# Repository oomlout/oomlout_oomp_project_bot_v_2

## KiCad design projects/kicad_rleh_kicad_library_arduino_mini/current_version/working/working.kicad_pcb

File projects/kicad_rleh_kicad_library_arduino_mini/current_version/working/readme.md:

# kicad_library
 
## summary 
* id: kicad_rleh_kicad_library_arduino_mini
* user: kicad_rleh
* name: kicad_library
* board: arduino_mini
* repo: https://github.com/kicad-rleh/kicad-library
* src_file_repo_kicad_pcb: template/Arduino_Mini/Arduino_Mini.kicad_pcb
* src_file_repo_kicad_pcb_link: https://github.com/kicad-rleh/kicad-library/tree/master/template/Arduino_Mini/Arduino_Mini.kicad_pcb

* src_file_repo_sch: template/Arduino_Mini/Arduino_Mini.sch
* src_file_repo_sch_link: https://github.com/kicad-rleh/kicad-library/tree/master/template/Arduino_Mini/Arduino_Mini.sch
* full details link: https://github.com/oomlout/oomlout_oomp_project_bot_v_2/tree/main/projects/kicad_rleh_kicad_library_arduino_mini/current_version/working

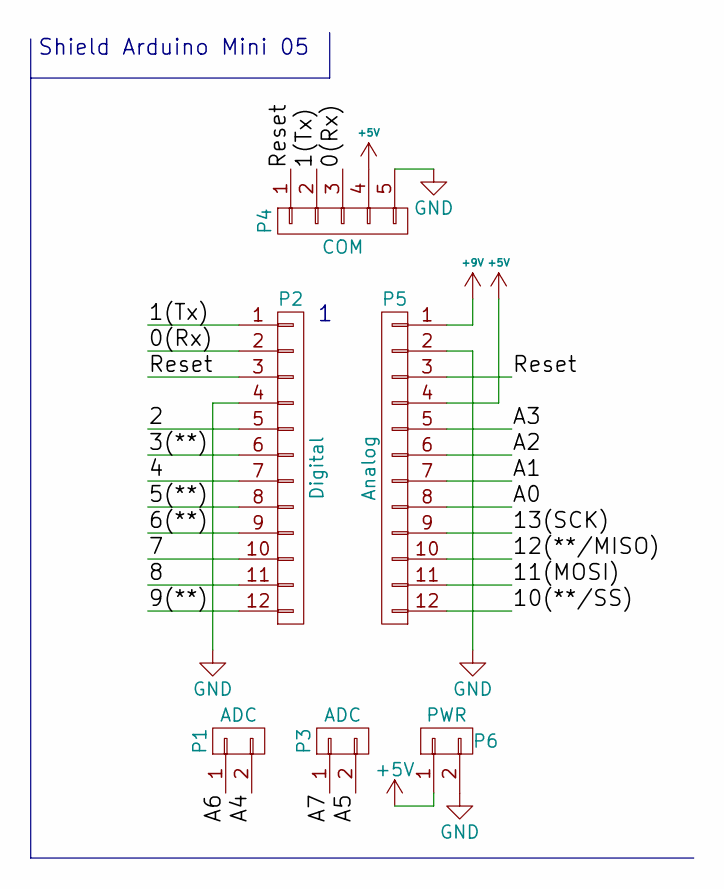
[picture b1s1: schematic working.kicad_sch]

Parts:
P1, P3: ADC; Socket_Strip_Arduino_1x02
P2: Digital; Socket_Strip_Arduino_1x12
P4: COM; Socket_Strip_Arduino_1x05
P5: Analog; Socket_Strip_Arduino_1x12
P6: PWR; Socket_Strip_Arduino_1x02

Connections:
+5V: P4.4, P5.4, P6.1
+9V: P5.1
/0(Rx): P2.2, P4.3
/1(Tx): P2.1, P4.2
/2: P2.5
/3(**): P2.6
/4: P2.7
/5(**): P2.8
/6(**): P2.9
/7: P2.10
/8: P2.11
/9(**): P2.12
/10(**/SS): P5.12
/11(MOSI): P5.11
/12(**/MISO): P5.10
/13(SCK): P5.9
/A0: P5.8
/A1: P5.7
/A2: P5.6
/A3: P5.5
/A4: P1.2
/A5: P3.2
/A6: P1.1
/A7: P3.1
/Reset: P2.3, P4.1, P5.3
GND: P2.4, P4.5, P5.2, P6.2

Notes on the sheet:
Shield Arduino Mini 05

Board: 2 copper layers, 6 parts (0 on the bottom side), 5 nets, no tracks yet.

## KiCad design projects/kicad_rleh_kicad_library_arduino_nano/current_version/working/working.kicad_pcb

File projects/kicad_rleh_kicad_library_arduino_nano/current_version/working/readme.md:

# kicad_library
 
## summary 
* id: kicad_rleh_kicad_library_arduino_nano
* user: kicad_rleh
* name: kicad_library
* board: arduino_nano
* repo: https://github.com/kicad-rleh/kicad-library
* src_file_repo_kicad_pcb: template/Arduino_Nano/Arduino_Nano.kicad_pcb
* src_file_repo_kicad_pcb_link: https://github.com/kicad-rleh/kicad-library/tree/master/template/Arduino_Nano/Arduino_Nano.kicad_pcb

* src_file_repo_sch: template/Arduino_Nano/Arduino_Nano.sch
* src_file_repo_sch_link: https://github.com/kicad-rleh/kicad-library/tree/master/template/Arduino_Nano/Arduino_Nano.sch
* full details link: https://github.com/oomlout/oomlout_oomp_project_bot_v_2/tree/main/projects/kicad_rleh_kicad_library_arduino_nano/current_version/working

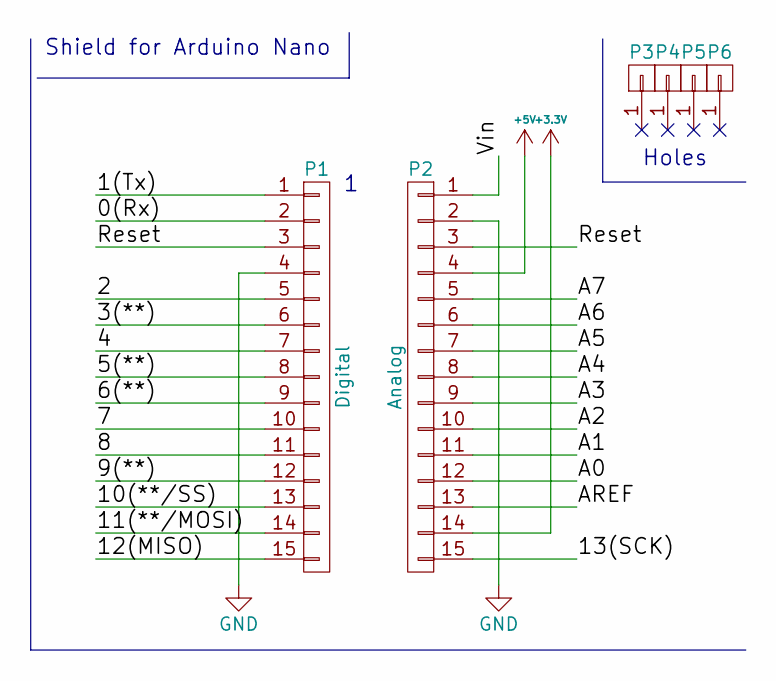
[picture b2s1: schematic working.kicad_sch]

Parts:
P1: Digital; Socket_Strip_Arduino_1x15
P2: Analog; Socket_Strip_Arduino_1x15
P3, P4, P5, P6: CONN_01X01; 1pin_Nano

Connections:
+3V3: P2.14
+5V: P2.4
/0(Rx): P1.2
/1(Tx): P1.1
/2: P1.5
/3(**): P1.6
/4: P1.7
/5(**): P1.8
/6(**): P1.9
/7: P1.10
/8: P1.11
/9(**): P1.12
/10(**/SS): P1.13
/11(**/MOSI): P1.14
/12(MISO): P1.15
/13(SCK): P2.15
/A0: P2.12
/A1: P2.11
/A2: P2.10
/A3: P2.9
/A4: P2.8
/A5: P2.7
/A6: P2.6
/A7: P2.5
/AREF: P2.13
/Reset: P1.3, P2.3
/Vin: P2.1
GND: P1.4, P2.2

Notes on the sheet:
Holes
Shield for Arduino Nano

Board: 2 copper layers, 6 parts (0 on the bottom side), 2 nets, no tracks yet.

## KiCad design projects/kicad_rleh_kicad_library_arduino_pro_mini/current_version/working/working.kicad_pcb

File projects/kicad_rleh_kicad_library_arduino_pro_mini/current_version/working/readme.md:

# kicad_library
 
## summary 
* id: kicad_rleh_kicad_library_arduino_pro_mini
* user: kicad_rleh
* name: kicad_library
* board: arduino_pro_mini
* repo: https://github.com/kicad-rleh/kicad-library
* src_file_repo_kicad_pcb: template/Arduino_Pro_Mini/Arduino_Pro_Mini.kicad_pcb
* src_file_repo_kicad_pcb_link: https://github.com/kicad-rleh/kicad-library/tree/master/template/Arduino_Pro_Mini/Arduino_Pro_Mini.kicad_pcb

* src_file_repo_sch: template/Arduino_Pro_Mini/Arduino_Pro_Mini.sch
* src_file_repo_sch_link: https://github.com/kicad-rleh/kicad-library/tree/master/template/Arduino_Pro_Mini/Arduino_Pro_Mini.sch
* full details link: https://github.com/oomlout/oomlout_oomp_project_bot_v_2/tree/main/projects/kicad_rleh_kicad_library_arduino_pro_mini/current_version/working

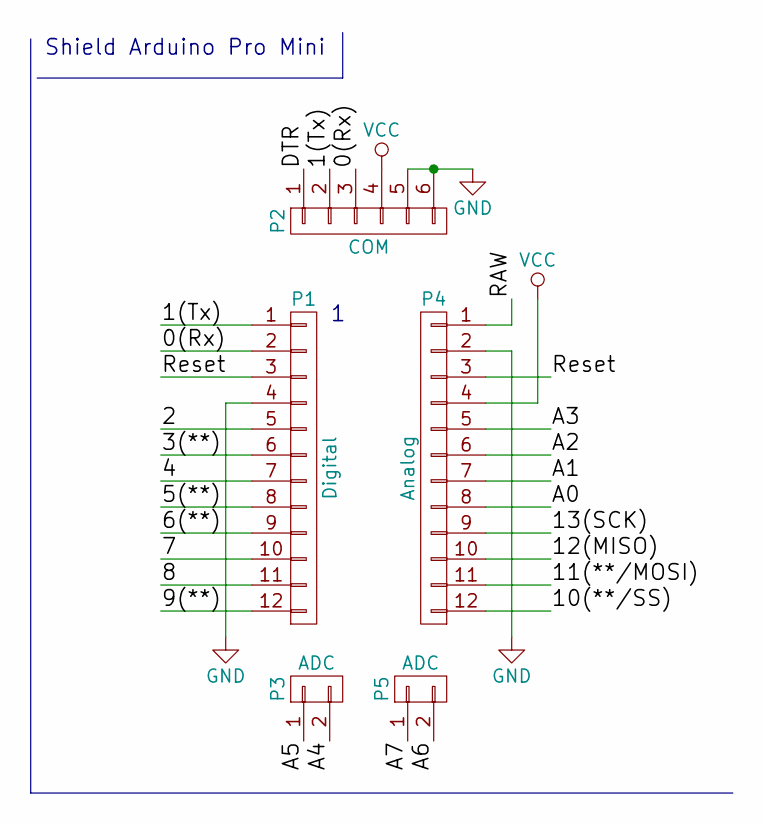
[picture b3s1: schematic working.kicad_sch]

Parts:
P1: Digital; Socket_Strip_Arduino_1x12
P2: COM; Socket_Strip_Arduino_1x06
P3, P5: ADC; Socket_Strip_Arduino_1x02
P4: Analog; Socket_Strip_Arduino_1x12

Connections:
/0(Rx): P1.2, P2.3
/1(Tx): P1.1, P2.2
/2: P1.5
/3(**): P1.6
/4: P1.7
/5(**): P1.8
/6(**): P1.9
/7: P1.10
/8: P1.11
/9(**): P1.12
/10(**/SS): P4.12
/11(**/MOSI): P4.11
/12(MISO): P4.10
/13(SCK): P4.9
/A0: P4.8
/A1: P4.7
/A2: P4.6
/A3: P4.5
/A4: P3.2
/A5: P3.1
/A6: P5.2
/A7: P5.1
/DTR: P2.1
/RAW: P4.1
/Reset: P1.3, P4.3
GND: P1.4, P2.5, P2.6, P4.2
VCC: P2.4, P4.4

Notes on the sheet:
Shield Arduino Pro Mini

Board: 2 copper layers, 5 parts (0 on the bottom side), 5 nets, no tracks yet.

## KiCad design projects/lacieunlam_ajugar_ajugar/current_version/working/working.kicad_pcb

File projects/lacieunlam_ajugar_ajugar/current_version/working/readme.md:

# ajugar
 
## summary 
* id: lacieunlam_ajugar_ajugar
* user: lacieunlam
* name: ajugar
* board: ajugar
* repo: https://github.com/LacieUnlam/Ajugar
* src_file_repo_kicad_pcb: AjugarV2/Ajugar.kicad_pcb
* src_file_repo_kicad_pcb_link: https://github.com/LacieUnlam/Ajugar/tree/master/AjugarV2/Ajugar.kicad_pcb

* src_file_repo_sch: AjugarV2/Ajugar.sch
* src_file_repo_sch_link: https://github.com/LacieUnlam/Ajugar/tree/master/AjugarV2/Ajugar.sch
* full details link: https://github.com/oomlout/oomlout_oomp_project_bot_v_2/tree/main/projects/lacieunlam_ajugar_ajugar/current_version/working

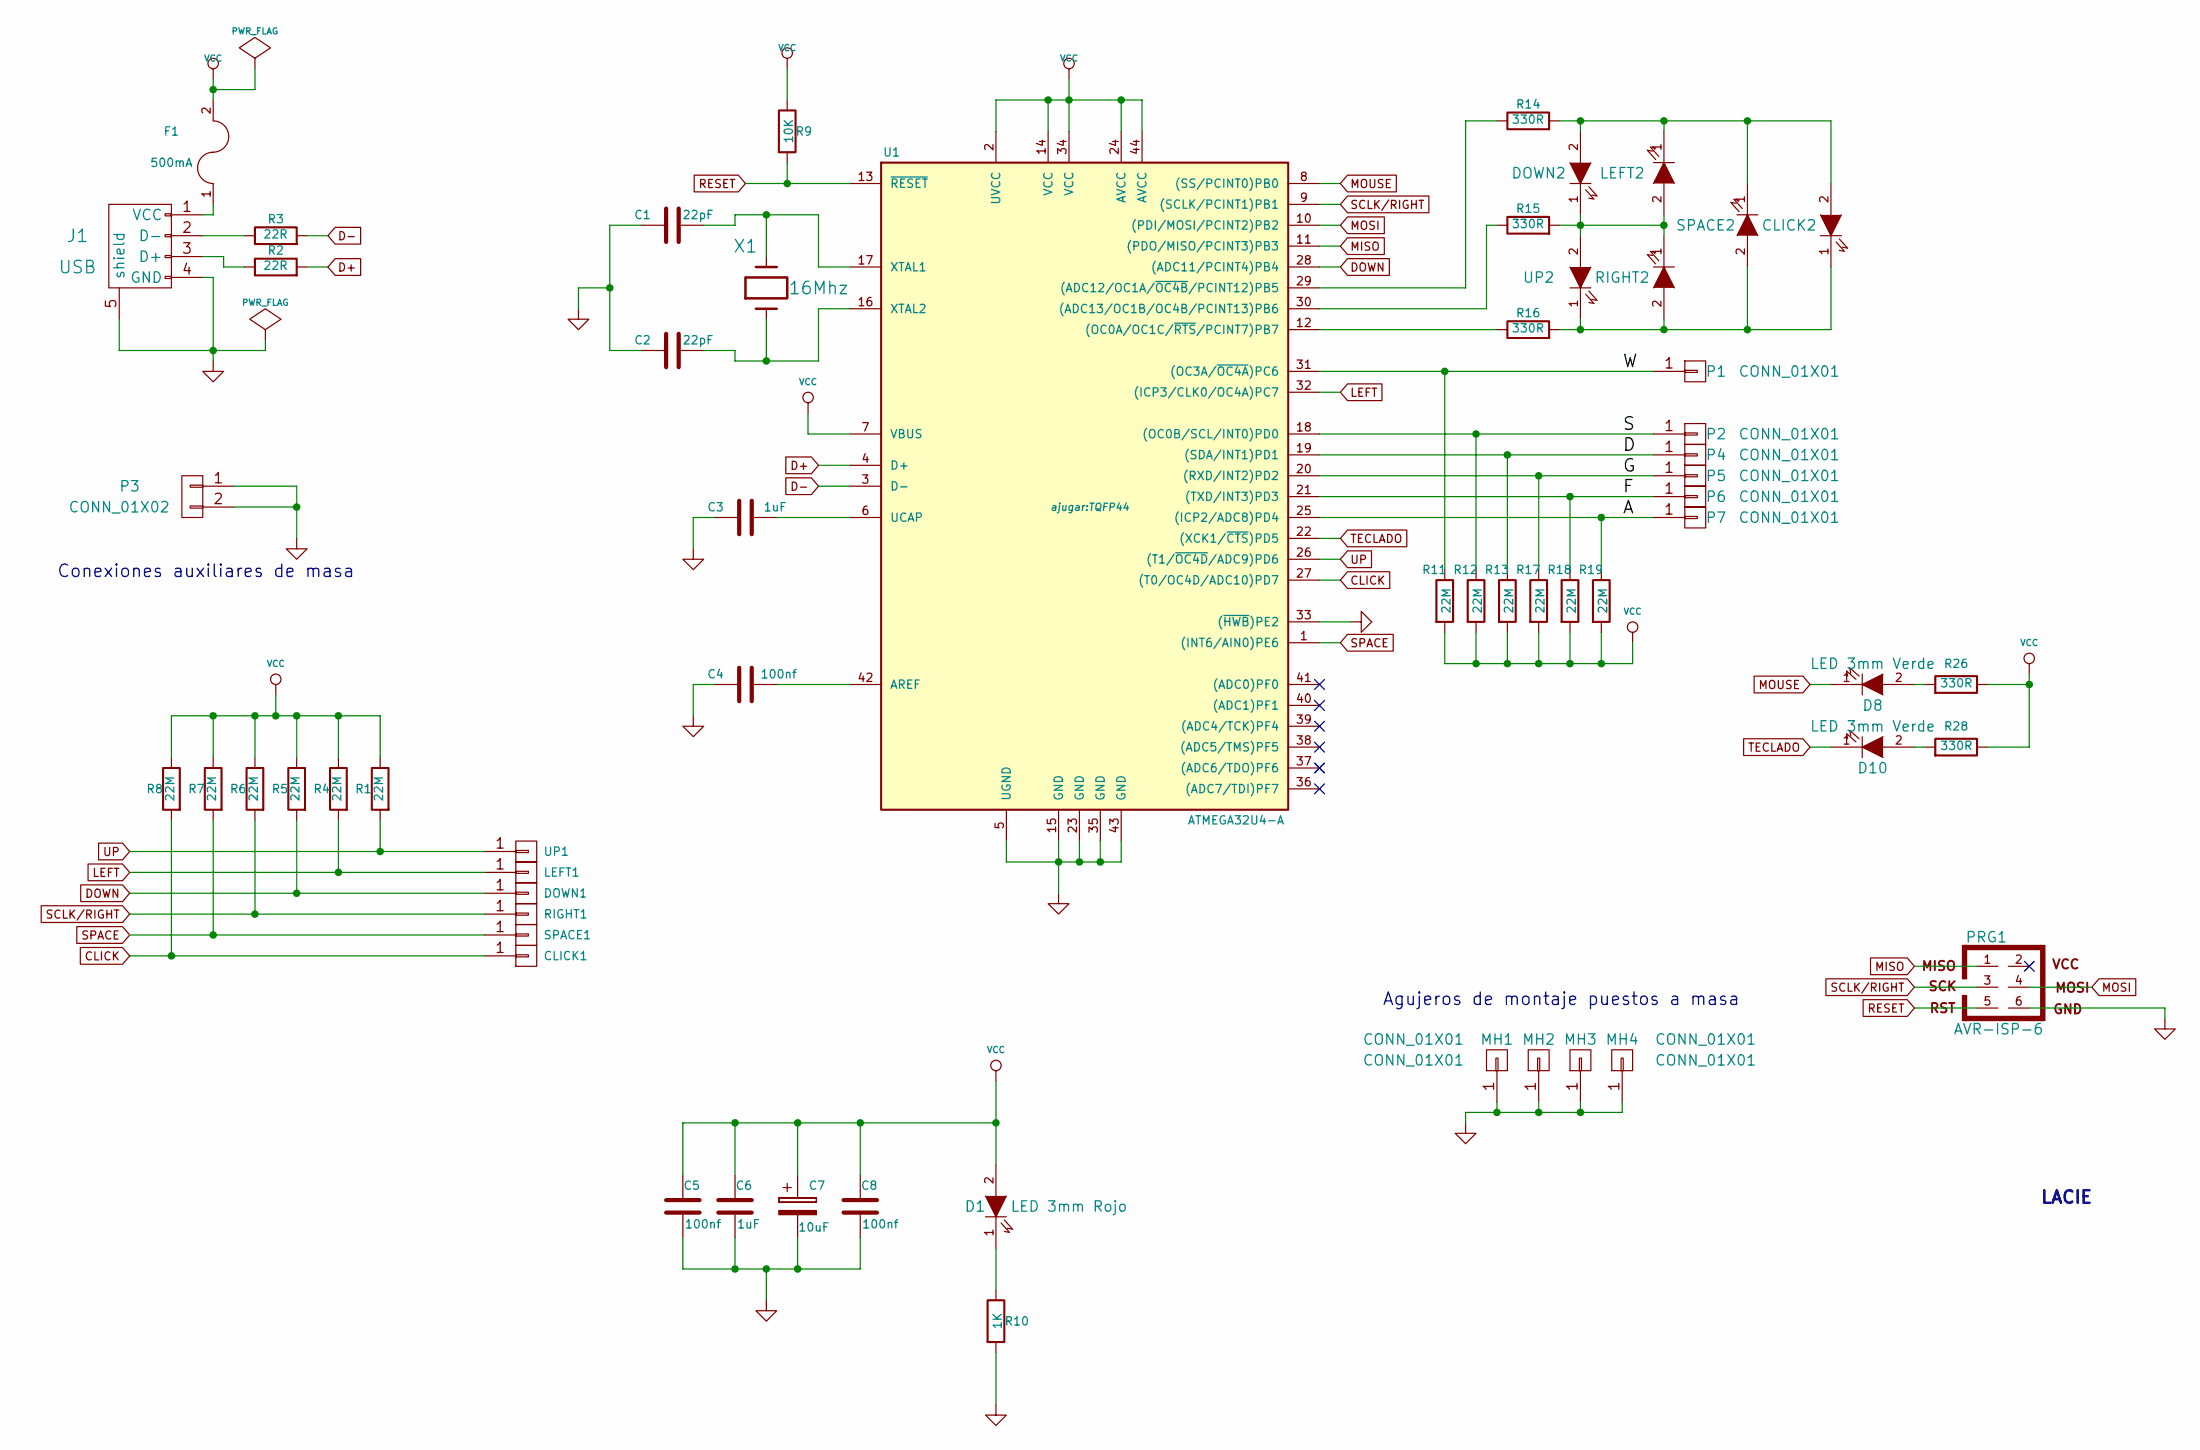
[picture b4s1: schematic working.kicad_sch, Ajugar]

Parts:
C1, C2: 22pF; C1
C3: 1uF; C1
C4, C5, C8: 100nf; C1
C6: 1uF; C1V5
C7: 10uF; C1V5
CLICK1: CONN_1; 1pin
CLICK2: LED 3mm Verde; LED-3MM
D1: LED 3mm Rojo; LED-3MM
D8, D10: LED 3mm Verde; LED-3MM
DOWN1: CONN_1; 1pin
DOWN2: LED 3mm Verde; LED-3MM
F1: 500mA; R4
J1: USB; USB_B
LEFT1: CONN_1; 1pin
LEFT2: LED 3mm Verde; LED-3MM
MH1, MH2, MH3, MH4: CONN_01X01; 1pin
P1, P2, P4, P5, P6, P7: CONN_01X01; 1pin
P3: CONN_01X02; Pin_Header_Straight_1x02
PRG1: AVR-ISP-6; pin_array_3x2
R1, R4, R5, R6, R7, R8, R11, R12, R13, R17, R18, R19: 22M; R3
R2, R3: 22R; R4
R9: 10K; R4
R10: 1K; R4
R14, R15, R28: 330R; R3-5
R16, R26: 330R; R4
RIGHT1: CONN_1; 1pin
RIGHT2: LED 3mm Verde; LED-3MM
SPACE1: CONN_1; 1pin
SPACE2: LED 3mm Verde; LED-3MM
U1: ATMEGA32U4-A; TQFP44
UP1: CONN_1; 1pin
UP2: LED 3mm Verde; LED-3MM
X1: 16Mhz; HC-18UV

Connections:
/A: P7.1, R19.1, U1.25 ((ICP2/ADC8)PD4)
/D: P4.1, R13.1, U1.19 ((SDA/INT1)PD1)
/F: P6.1, R18.1, U1.21 ((TXD/INT3)PD3)
/G: P5.1, R17.1, U1.20 ((RXD/INT2)PD2)
/S: P2.1, R12.1, U1.18 ((OC0B/SCL/INT0)PD0)
/W: P1.1, R11.1, U1.31 ((OC3A/~OC4A)PC6)
CLICK: CLICK1.1, R8.2, U1.27 ((T0/OC4D/ADC10)PD7)
D+: R2.2, U1.4 (D+)
D-: R3.2, U1.3 (D-)
DOWN: DOWN1.1, R5.2, U1.28 ((ADC11/PCINT4)PB4)
GND: C1.1, C2.1, C3.1, C4.1, C5.2, C6.2, C7.2, C8.2, J1.4 (GND), J1.5 (shield), MH1.1, MH2.1, MH3.1, MH4.1, P3.1, P3.2, PRG1.6, R10.2, U1.5 (UGND), U1.15 (GND), U1.23 (GND), U1.33 ((~HWB)PE2), U1.35 (GND), U1.43 (GND)
LEFT: LEFT1.1, R4.2, U1.32 ((ICP3/CLK0/OC4A)PC7)
MISO: PRG1.1, U1.11 ((PDO/MISO/PCINT3)PB3)
MOSI: PRG1.4, U1.10 ((PDI/MOSI/PCINT2)PB2)
MOUSE: D8.1 (K), U1.8 ((SS/PCINT0)PB0)
unnamed: C1.2, U1.17 (XTAL1), X1.2
unnamed: C2.2, U1.16 (XTAL2), X1.1
unnamed: C3.2, U1.6 (UCAP)
unnamed: C4.2, U1.42 (AREF)
unnamed: CLICK2.1 (K), R16.2, RIGHT2.2 (A), SPACE2.2 (A), UP2.1 (K)
unnamed: CLICK2.2 (A), DOWN2.2 (A), LEFT2.1 (K), R14.2, SPACE2.1 (K)
unnamed: D1.1 (K), R10.1
unnamed: D8.2 (A), R26.2
unnamed: D10.2 (A), R28.2
unnamed: DOWN2.1 (K), LEFT2.2 (A), R15.2, RIGHT2.1 (K), UP2.2 (A)
unnamed: F1.1, J1.1 (VCC)
unnamed: J1.2 (D-), R3.1
unnamed: J1.3 (D+), R2.1
unnamed: R14.1, U1.29 ((ADC12/OC1A/~OC4B/PCINT12)PB5)
unnamed: R15.1, U1.30 ((ADC13/OC1B/OC4B/PCINT13)PB6)
unnamed: R16.1, U1.12 ((OC0A/OC1C/~RTS/PCINT7)PB7)
RESET: PRG1.5, R9.2, U1.13 (~RESET)
SCLK/RIGHT: PRG1.3, R6.2, RIGHT1.1, U1.9 ((SCLK/PCINT1)PB1)
SPACE: R7.2, SPACE1.1, U1.1 ((INT6/AIN0)PE6)
TECLADO: D10.1 (K), U1.22 ((XCK1/~CTS)PD5)
UP: R1.2, U1.26 ((T1/~OC4D/ADC9)PD6), UP1.1
VCC: C5.1, C6.1, C7.1, C8.1, D1.2 (A), F1.2, R1.1, R4.1, R5.1, R6.1, R7.1, R8.1, R9.1, R11.2, R12.2, R13.2, R17.2, R18.2, R19.2, R26.1, R28.1, U1.2 (UVCC), U1.7 (VBUS), U1.14 (VCC), U1.24 (AVCC), U1.34 (VCC), U1.44 (AVCC)

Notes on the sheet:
LACIE
Agujeros de montaje puestos a masa
Conexiones auxiliares de masa

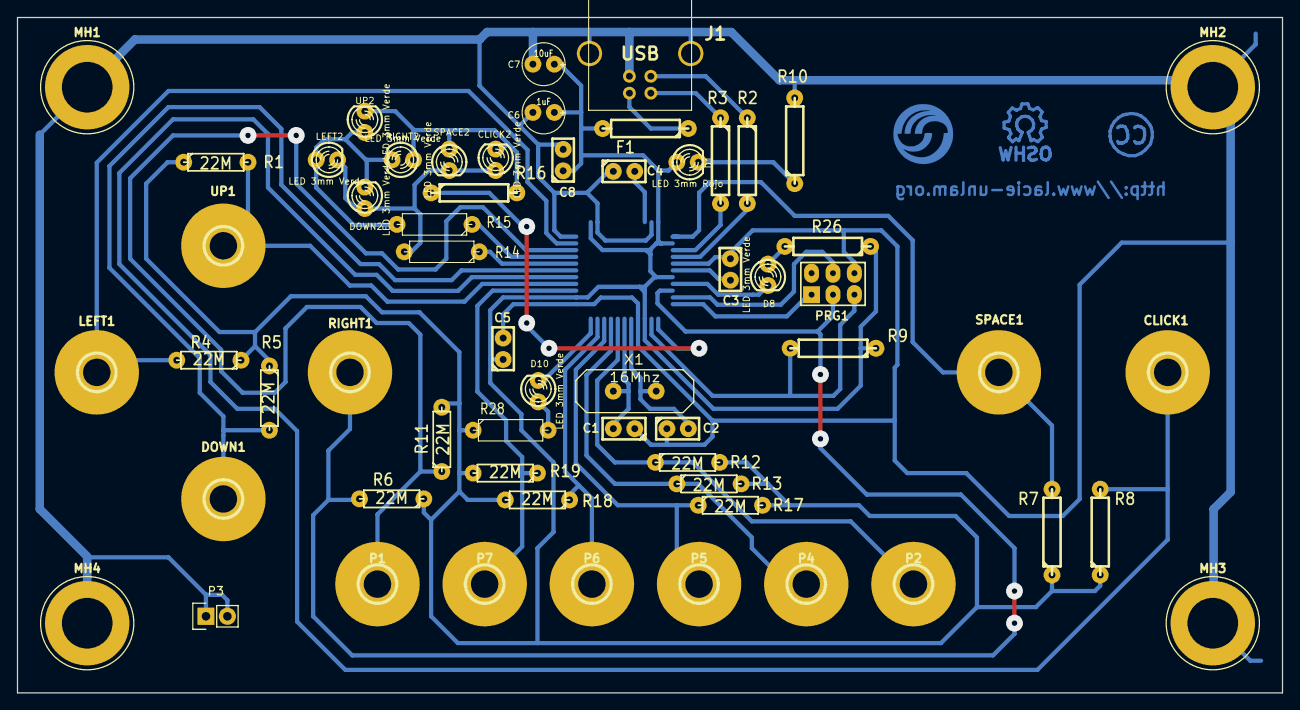
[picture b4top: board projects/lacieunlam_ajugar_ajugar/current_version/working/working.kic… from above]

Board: 2 copper layers, 149.9 x 80.0 mm, 60 parts (1 on the bottom side), 37 nets.

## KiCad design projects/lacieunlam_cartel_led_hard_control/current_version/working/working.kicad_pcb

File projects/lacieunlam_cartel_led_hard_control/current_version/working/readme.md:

# cartel_led
 
## summary 
* id: lacieunlam_cartel_led_hard_control
* user: lacieunlam
* name: cartel_led
* board: hard_control
* repo: https://github.com/LacieUnlam/cartel-led
* src_file_repo_kicad_pcb: Hard/control/3 lineas/hard_control.kicad_pcb
* src_file_repo_kicad_pcb_link: https://github.com/LacieUnlam/cartel-led/tree/master/Hard/control/3 lineas/hard_control.kicad_pcb

* src_file_repo_sch: Hard/control/3 lineas/hard_control.sch
* src_file_repo_sch_link: https://github.com/LacieUnlam/cartel-led/tree/master/Hard/control/3 lineas/hard_control.sch
* full details link: https://github.com/oomlout/oomlout_oomp_project_bot_v_2/tree/main/projects/lacieunlam_cartel_led_hard_control/current_version/working

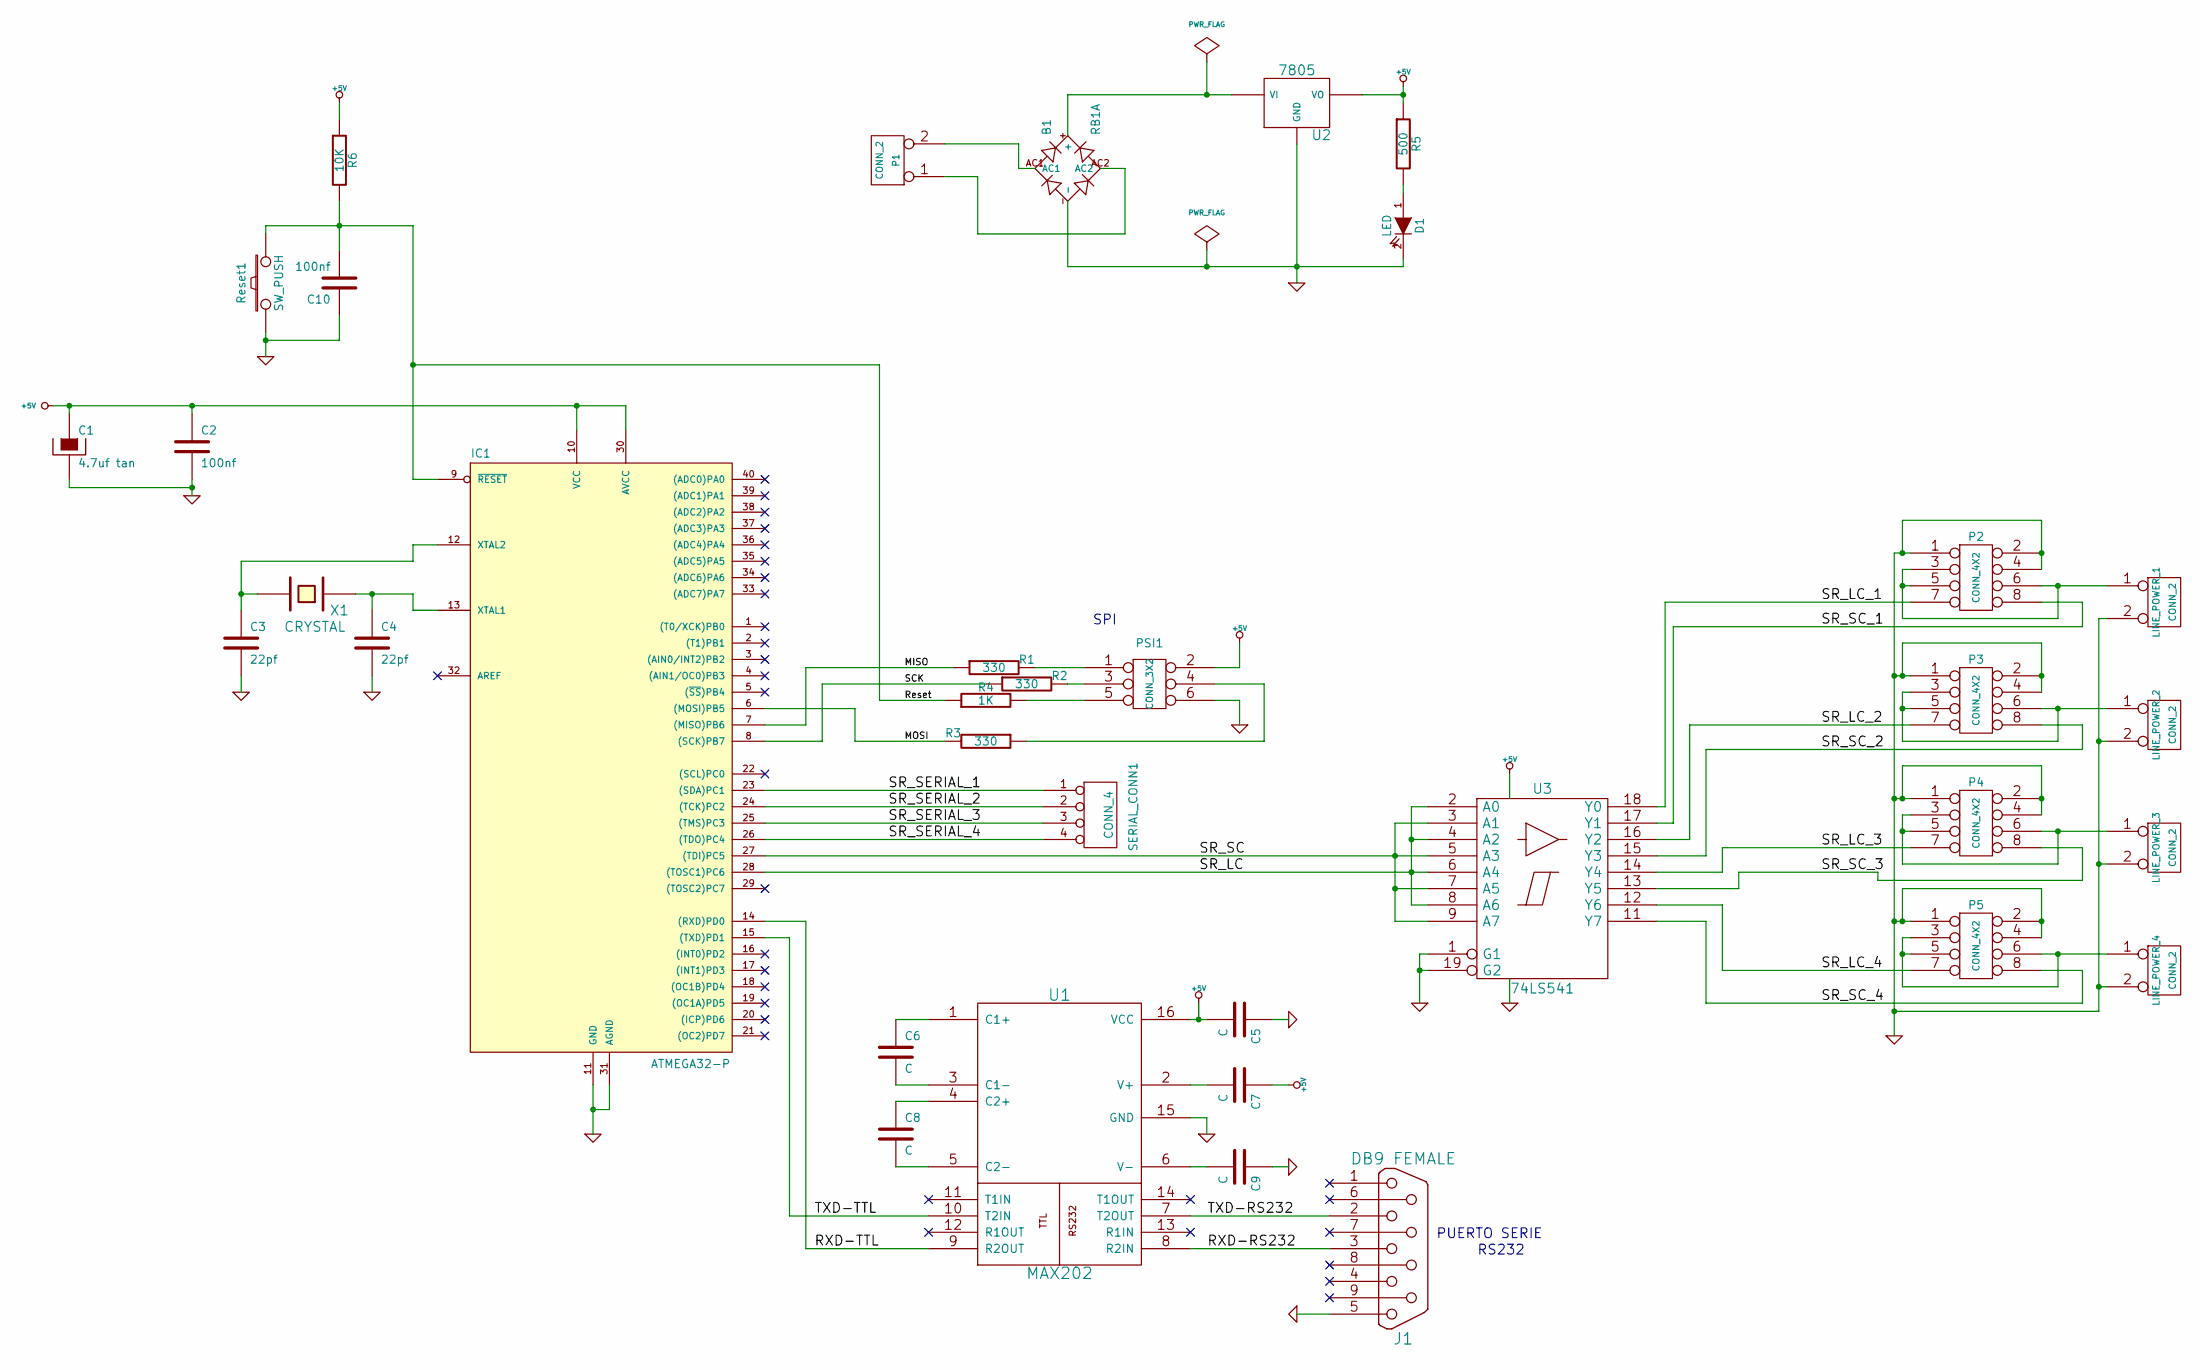
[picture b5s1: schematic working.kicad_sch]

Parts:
B1: RB1A; rectifier-RB1A
C1: 4.7uf tan
C2, C10: 100nf
C3, C4: 22pf
C5, C6, C7, C8, C9: C
D1: LED
IC1: ATMEGA32-P; DIL40
J1: DB9 FEMALE
LINE_POWER_1, LINE_POWER_2, LINE_POWER_3, LINE_POWER_4: CONN_2
P1: CONN_2
P2, P3, P4, P5: CONN_4X2
PSI1: CONN_3X2
R1, R2, R3: 330
R4: 1K
R5: 500
R6: 10K
Reset1: SW_PUSH
SERIAL_CONN1: CONN_4
U1: MAX202
U2: 7805
U3: 74LS541
X1: CRYSTAL

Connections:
+5V: C1.1, C2.1, C5.2, C7.1, IC1.10 (VCC), IC1.30 (AVCC), PSI1.2, R5.1, R6.1, U1.16 (VCC), U2.VO, U3.20 (VCC)
/MISO: IC1.7 ((MISO)PB6), R1.1
/MOSI: IC1.6 ((MOSI)PB5), R3.2
/RXD-RS232: J1.3, U1.8 (R2IN)
/RXD-TTL: IC1.14 ((RXD)PD0), U1.9 (R2OUT)
/Reset: C10.2, IC1.9 (~RESET), R4.1, R6.2, Reset1.2
/SCK: IC1.8 ((SCK)PB7), R2.1
/SR_LC: IC1.28 ((TOSC1)PC6), U3.2 (A0), U3.4 (A2), U3.6 (A4), U3.8 (A6)
/SR_LC_1: P2.7, U3.18 (Y0)
/SR_LC_2: P3.7, U3.16 (Y2)
/SR_LC_3: P4.7, U3.14 (Y4)
/SR_LC_4: P5.7, U3.12 (Y6)
/SR_SC: IC1.27 ((TDI)PC5), U3.3 (A1), U3.5 (A3), U3.7 (A5), U3.9 (A7)
/SR_SC_1: P2.8, U3.17 (Y1)
/SR_SC_2: P3.8, U3.15 (Y3)
/SR_SC_3: P4.8, U3.13 (Y5)
/SR_SC_4: P5.8, U3.11 (Y7)
/SR_SERIAL_1: IC1.23 ((SDA)PC1), SERIAL_CONN1.1
/SR_SERIAL_2: IC1.24 ((TCK)PC2), SERIAL_CONN1.2
/SR_SERIAL_3: IC1.25 ((TMS)PC3), SERIAL_CONN1.3
/SR_SERIAL_4: IC1.26 ((TDO)PC4), SERIAL_CONN1.4
/TXD-RS232: J1.2, U1.7 (T2OUT)
/TXD-TTL: IC1.15 ((TXD)PD1), U1.10 (T2IN)
GND: B1.-, C1.2, C2.2, C3.2, C4.2, C5.1, C9.1, C10.1, D1.2 (K), IC1.11 (GND), IC1.31 (AGND), J1.5, LINE_POWER_1.2 (PM), LINE_POWER_2.2 (PM), LINE_POWER_3.2 (PM), LINE_POWER_4.2 (PM), P2.1, P2.2, P2.4, P3.1, P3.2, P3.4, P4.1, P4.2, P4.4, P5.1, P5.2, P5.4, PSI1.6, Reset1.1, U1.15 (GND), U2.GND, U3.1 (G1), U3.10 (GND), U3.19 (G2)
unnamed: LINE_POWER_3.1, P4.3, P4.5, P4.6
unnamed: LINE_POWER_2.1, P3.3, P3.5, P3.6
unnamed: C3.1, IC1.12 (XTAL2), X1.2
unnamed: LINE_POWER_4.1, P5.3, P5.5, P5.6
unnamed: D1.1 (A), R5.2
unnamed: B1.+, U2.VI
unnamed: B1.AC2, P1.1
unnamed: B1.AC1, P1.2 (PM)
unnamed: PSI1.4, R3.1
unnamed: PSI1.5, R4.2
unnamed: PSI1.3, R2.2
unnamed: PSI1.1, R1.2
unnamed: C4.1, IC1.13 (XTAL1), X1.1
unnamed: C7.2, U1.2 (V+)
unnamed: C8.2, U1.5 (C2-)
unnamed: C8.1, U1.4 (C2+)
unnamed: C6.2, U1.3 (C1-)
unnamed: C6.1, U1.1 (C1+)
unnamed: C9.2, U1.6 (V-)
unnamed: LINE_POWER_1.1, P2.3, P2.5, P2.6

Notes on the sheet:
PUERTO SERIE
RS232
SPI

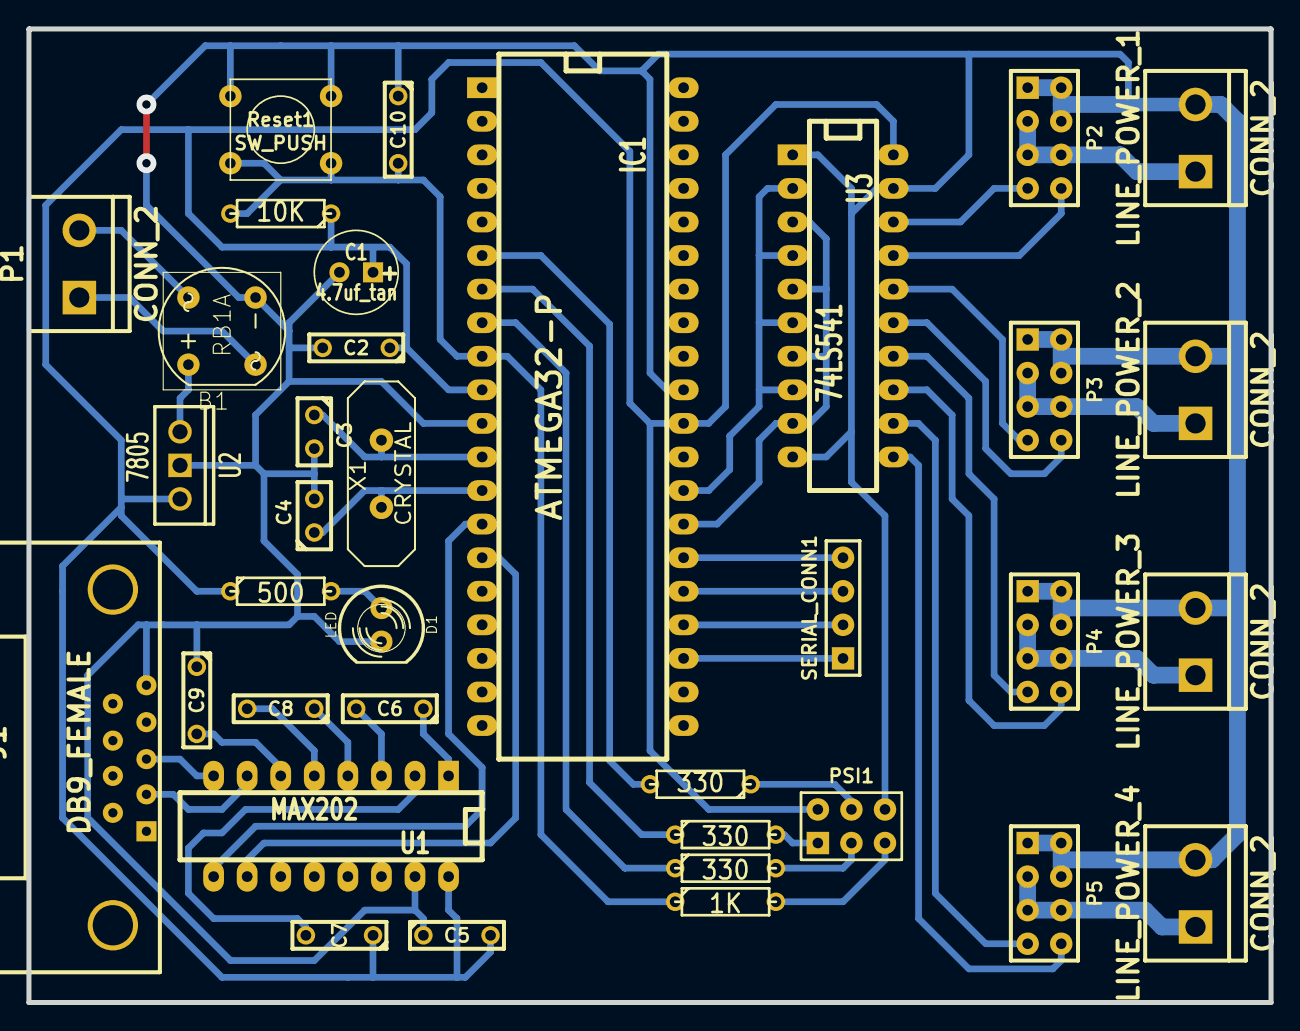
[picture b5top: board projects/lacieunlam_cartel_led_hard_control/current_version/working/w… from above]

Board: 2 copper layers, 94.0 x 73.7 mm, 36 parts (0 on the bottom side), 44 nets.

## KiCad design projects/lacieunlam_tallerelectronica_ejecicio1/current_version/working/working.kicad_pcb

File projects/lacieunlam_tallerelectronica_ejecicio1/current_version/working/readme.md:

# tallerelectronica
 
## summary 
* id: lacieunlam_tallerelectronica_ejecicio1
* user: lacieunlam
* name: tallerelectronica
* board: ejecicio1
* repo: https://github.com/LacieUnlam/TallerElectronica
* src_file_repo_kicad_pcb: 2016/Beninato/Ejecicio1.kicad_pcb
* src_file_repo_kicad_pcb_link: https://github.com/LacieUnlam/TallerElectronica/tree/master/2016/Beninato/Ejecicio1.kicad_pcb

* src_file_repo_sch: 2016/Beninato/Ejecicio1.sch
* src_file_repo_sch_link: https://github.com/LacieUnlam/TallerElectronica/tree/master/2016/Beninato/Ejecicio1.sch
* full details link: https://github.com/oomlout/oomlout_oomp_project_bot_v_2/tree/main/projects/lacieunlam_tallerelectronica_ejecicio1/current_version/working

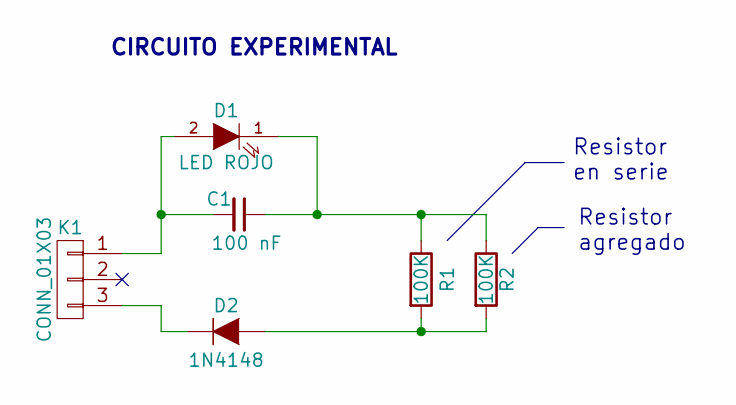
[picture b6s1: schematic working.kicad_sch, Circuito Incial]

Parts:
C1: 100 nF; C_Rect_L7_W3.5_P5
D1: LED ROJO; LED-3MM
D2: 1N4148; Diode_DO-35_SOD27_Horizontal_RM10
K1: CONN_01X03; bornier3
R1, R2: 100K; R3-LARGE_PADS

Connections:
unnamed: C1.1, D1.1 (K), R1.1, R2.1
unnamed: C1.2, D1.2 (A), K1.1
unnamed: D2.1 (K), K1.3
unnamed: D2.2 (A), R1.2, R2.2

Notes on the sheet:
CIRCUITO EXPERIMENTAL
Resistor en serie
Resistor agregado

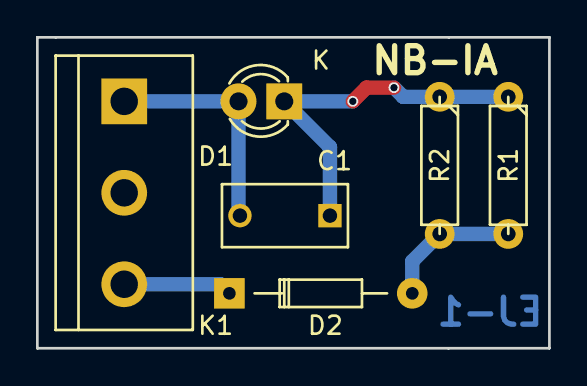
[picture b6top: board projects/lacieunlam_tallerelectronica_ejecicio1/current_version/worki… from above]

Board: 2 copper layers, 28.4 x 17.3 mm, 6 parts (0 on the bottom side), 4 nets.

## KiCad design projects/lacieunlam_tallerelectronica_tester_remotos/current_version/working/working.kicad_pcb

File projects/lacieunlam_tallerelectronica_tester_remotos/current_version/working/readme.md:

# tallerelectronica
 
## summary 
* id: lacieunlam_tallerelectronica_tester_remotos
* user: lacieunlam
* name: tallerelectronica
* board: tester_remotos
* repo: https://github.com/LacieUnlam/TallerElectronica
* src_file_repo_kicad_pcb: tester_remotos/tester_remotos.kicad_pcb
* src_file_repo_kicad_pcb_link: https://github.com/LacieUnlam/TallerElectronica/tree/master/tester_remotos/tester_remotos.kicad_pcb

* src_file_repo_sch: tester_remotos/tester_remotos.sch
* src_file_repo_sch_link: https://github.com/LacieUnlam/TallerElectronica/tree/master/tester_remotos/tester_remotos.sch
* full details link: https://github.com/oomlout/oomlout_oomp_project_bot_v_2/tree/main/projects/lacieunlam_tallerelectronica_tester_remotos/current_version/working

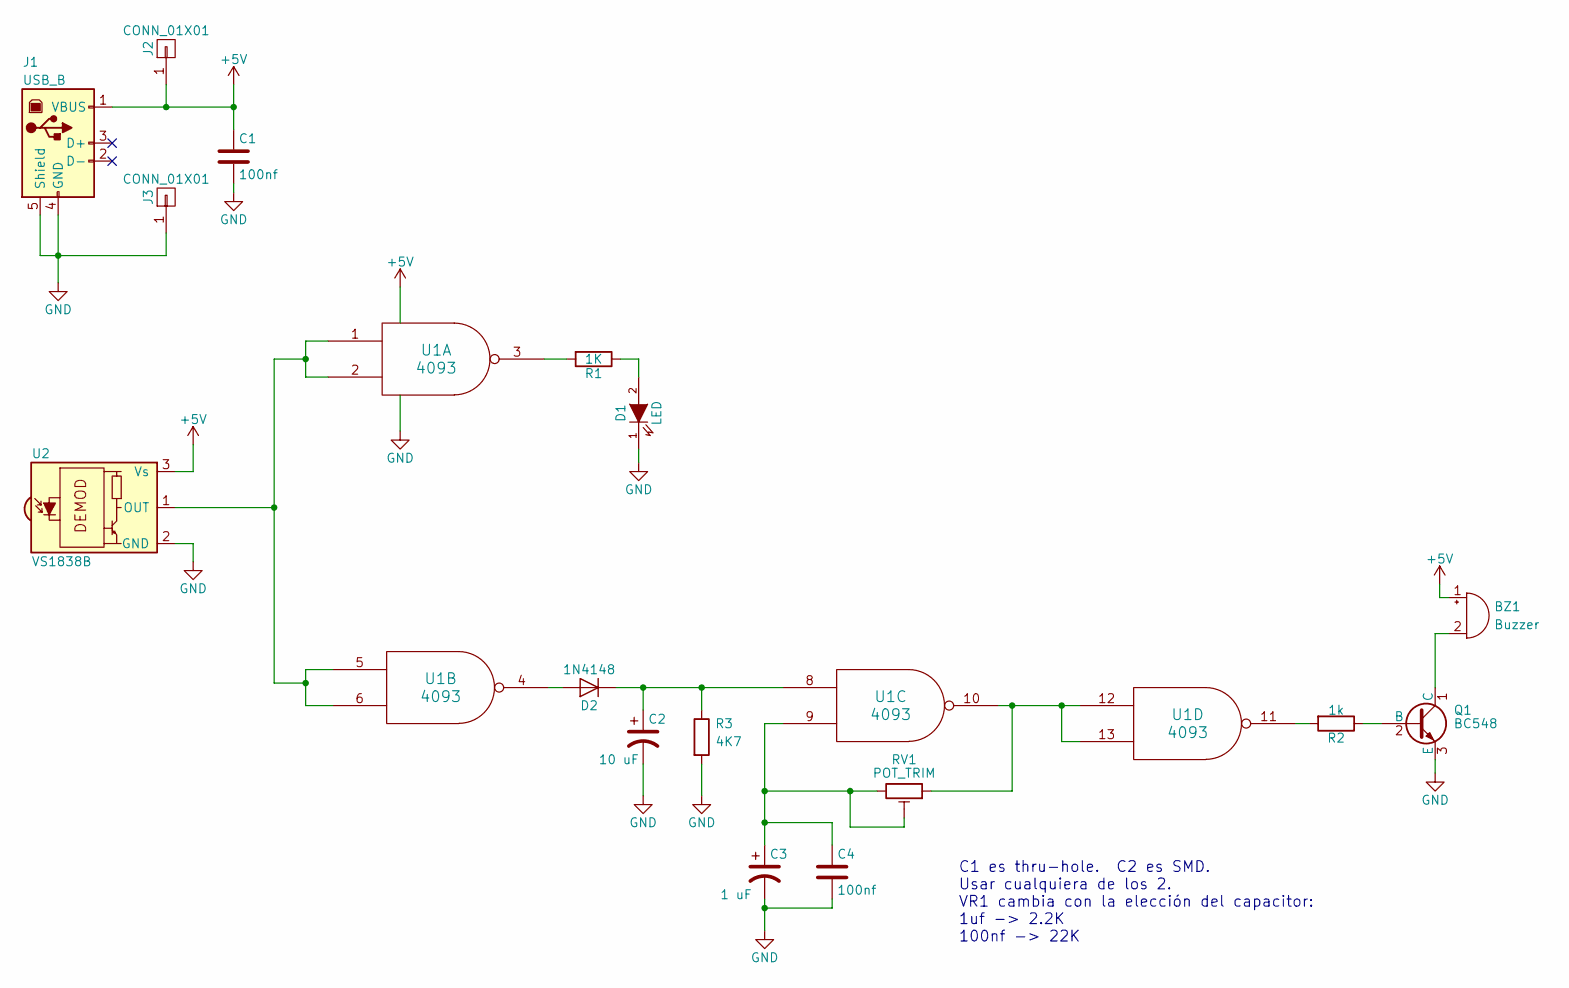
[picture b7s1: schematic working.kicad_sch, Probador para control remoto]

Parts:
BZ1: Buzzer; Buzzer_12x9.5RM7.6
C1: 100nf; C_Disc_D6_P5
C2: 10 uF; C_Radial_D6.3_L11.2_P2.5
C3: 1 uF; C_Radial_D6.3_L11.2_P2.5
C4: 100nf; C_0805_HandSoldering
D1: LED; LED-5MM
D2: 1N4148; Diode_DO-35_SOD27_Horizontal_RM10
J1: USB_B
J2, J3: CONN_01X01; SolderWirePad_single_1mmDrill
Q1: BC548; TO-92_Molded_Narrow
R1: 1K; Resistor_Horizontal_RM10mm
R2: 1k; Resistor_Horizontal_RM10mm
R3: 4K7; Resistor_Horizontal_RM10mm
RV1: POT_TRIM; trimmer_piher_pt10xv10
U1: 4093; DIP-14_W7.62mm_LongPads
U2: VS1838B

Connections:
+5V: BZ1.1 (-), C1.1, J1.1 (VBUS), J2.1, U1.14 (VDD), U2.3 (Vs)
GND: C1.2, C2.2, C3.2, C4.2, D1.1 (K), J1.4 (GND), J1.5 (Shield), J3.1, Q1.3 (E), R3.2, U1.7 (VSS), U2.2 (GND)
unnamed: BZ1.2 (+), Q1.1 (C)
unnamed: C2.1, D2.1 (K), R3.1, U1.8
unnamed: C3.1, C4.1, RV1.2, RV1.3, U1.9
unnamed: D1.2 (A), R1.1
unnamed: D2.2 (A), U1.4
unnamed: Q1.2 (B), R2.1
unnamed: R1.2, U1.3
unnamed: R2.2, U1.11
unnamed: RV1.1, U1.10, U1.12, U1.13
unnamed: U1.1, U1.2, U1.5, U1.6, U2.1 (OUT)

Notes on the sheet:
C1 es thru-hole. C2 es SMD. Usar cualquiera de los 2. VR1 cambia con la elección del capacitor: 1uf -> 2.2K 100nf -> 22K

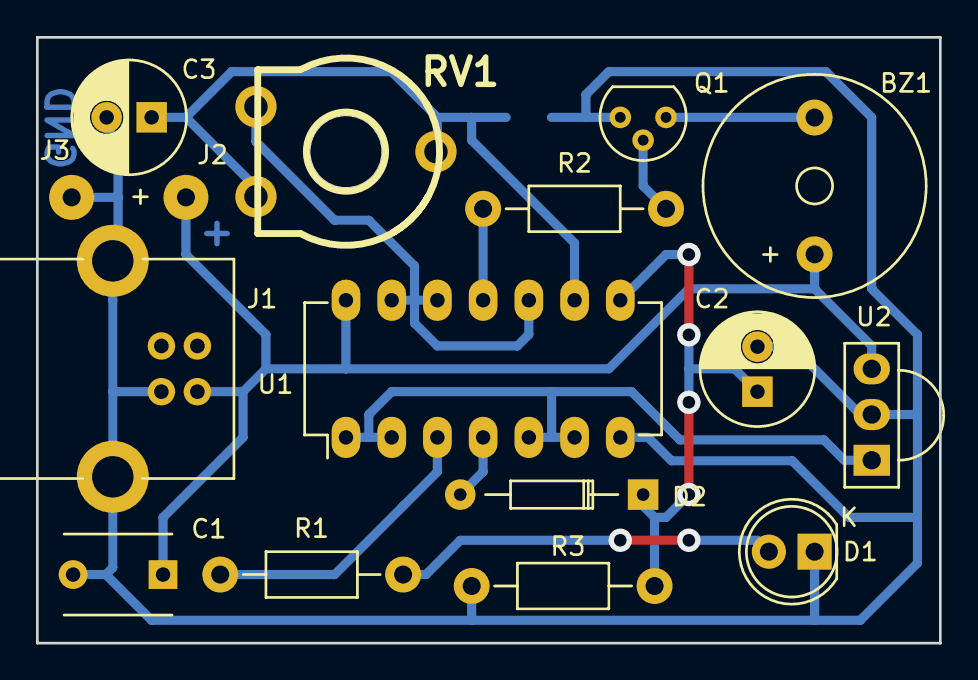
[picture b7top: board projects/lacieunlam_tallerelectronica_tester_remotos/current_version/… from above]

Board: 2 copper layers, 50.2 x 33.7 mm, 17 parts (1 on the bottom side), 12 nets.

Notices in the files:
projects/lacieunlam_ajugar_ajugar/current_version/working/working.kicad_pcb:
https://creativecommons.org/licenses/by-sa/4.0
Attribution-ShareAlike 4.0 International (CC BY-SA 4.0)
